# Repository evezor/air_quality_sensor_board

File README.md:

# Air Quality Sensor Board
board counts airborne particulate matter

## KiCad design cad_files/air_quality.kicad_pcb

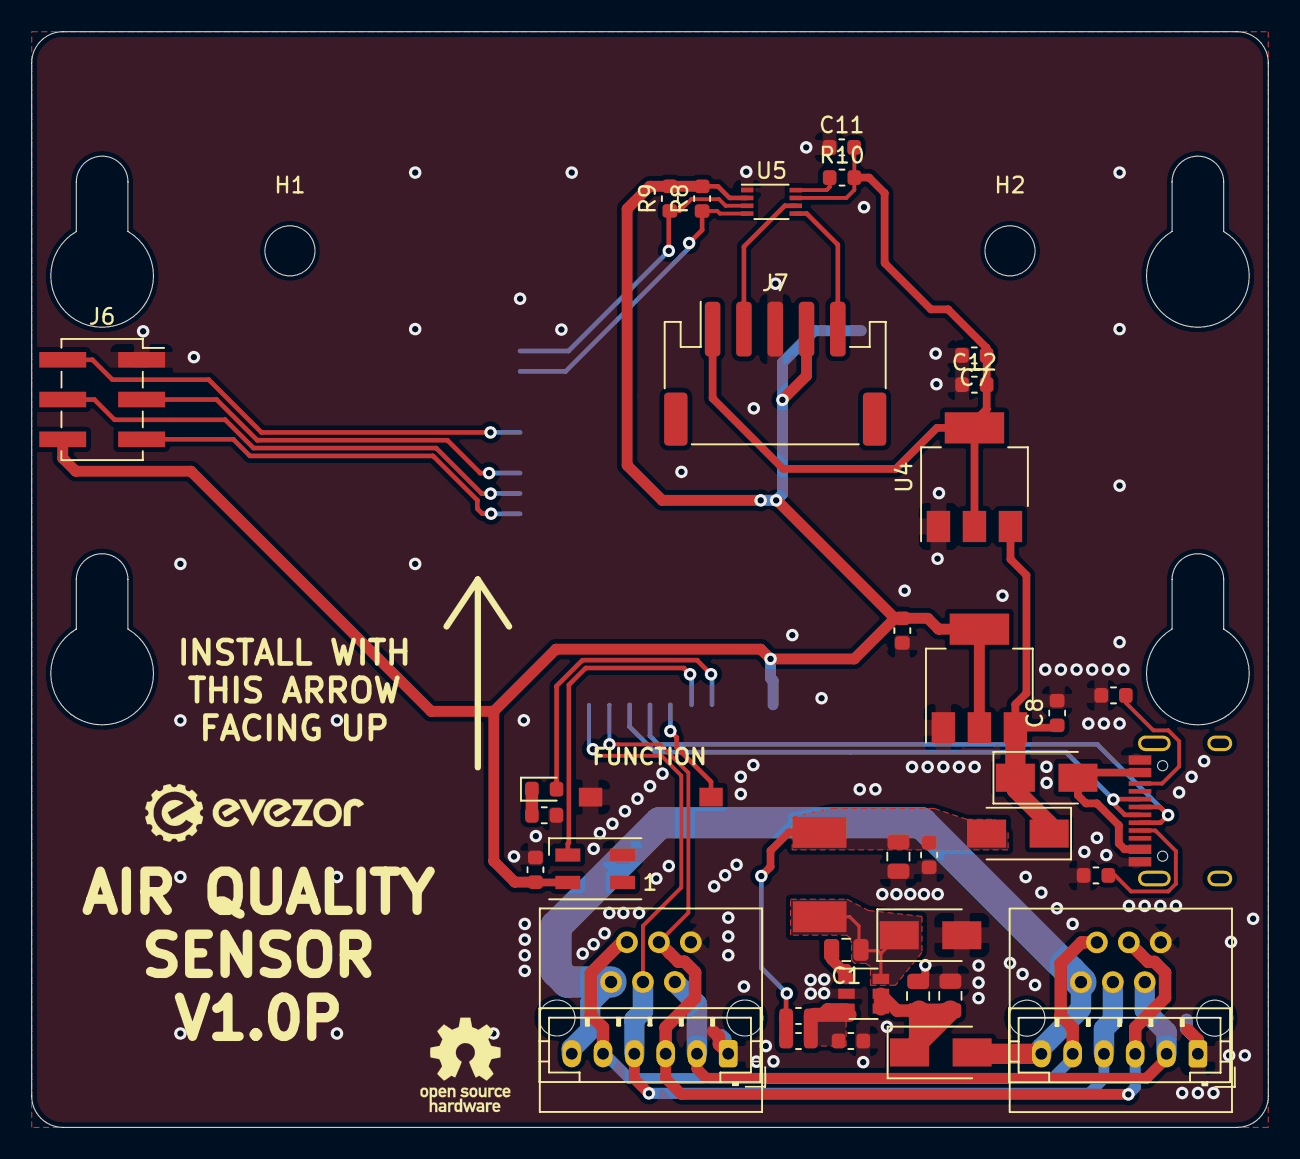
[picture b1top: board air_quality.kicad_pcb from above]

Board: 2 copper layers, 79.0 x 70.0 mm, 42 parts (1 on the bottom side), 32 nets.

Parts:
C1, C3: .1uF 100V; C_0805_2012Metric
C2, C5, C9, C10, C11, C12: .1uF; C_0603_1608Metric
C4: 4.7uF; C_0805_2012Metric
C6: 22uF; C_0805_2012Metric
C7, C8: 10uF; C_0603_1608Metric
D1, D2, D4, D5: SX35_SCHOTTKY; D_SMA
D3: LED; LED_0603_1608Metric
D6: SK6812MINI; LED_SK6812MINI_PLCC4_3.5x3.5mm_P1.75mm
H1: B5W-LD0101; AIR_QUALITY_B5W-LD0101
H2: MountingHole; MountingHole_3.2mm_M3
J1: USB_C_Receptacle_USB2.0; USB_C_Receptacle_HRO_TYPE-C-31-M-12
J2, J3: RJ11; RJ11_C189747_Horizontal
J4, J5: PH; JST_PH_B6B-PH-K_1x06_P2.00mm_Vertical
J6: Conn_02x03_Odd_Even; PinSocket_2x03_P2.54mm_Vertical_SMD
J7: Conn_01x05; JST_PH_S5B-PH-SM4-TB_1x05-1MP_P2.00mm_Horizontal
L1: 22uH; INDUCTOR_7.5X6.6_GCDA0630-220MC
R1: 10k; R_0603_1608Metric
R2: 82k; R_0603_1608Metric
R3, R4: 5.1k; R_0603_1608Metric
R5: 15k; R_0603_1608Metric
R8, R9: 2.2k; R_0603_1608Metric
R10: 200K; R_0603_1608Metric
SW1: SW_Push; SWITCH_2x3_SMD_TACTILE_GREEN
U1: SY8401ABC; SOT-23-6
U2: AMS1117-3.3; SOT-223-3_TabPin2
U3: EDGE_STM32F405_CPU_V1; EDGE_STAMP
U4: AMS1117-5.0; SOT-223-3_TabPin2
U5: LEVEL_SHIFTER_PCA9306; VSSOP-8_2.3x2mm_P0.5mm

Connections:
+3V3: C9.2, C10.1, D6.4, J6.6, J7.4, R8.2, R9.2, U2.2, U3.1, U3.18, U5.2
+5V: C7.1, C11.2, C12.2, J7.1, R10.2, U4.2, U5.7
/BOOT: J6.3, U3.36
/CAN_H: J2.3, J3.3, J4.3, J5.3, U3.26
/CAN_L: J2.4, J3.4, J4.4, J5.4, U3.27
/CC1: J1.A5, R4.1
/CC2: J1.B5, R3.1
/D+: J1.A6, J1.B6, U3.25
/D-: J1.A7, J1.B7, U3.24
/FD_H: J2.2, J3.2, J4.2, J5.2
/FD_L: J2.5, J3.5, J4.5, J5.5
/FUNCTION_BUTTON: SW1.1, U3.23
/HBT_LED: D3.2, U3.21
/NEO_STATUS: D6.3, U3.22
/OLED_SCL: J6.5, U3.34
/OLED_SDA: J6.4, U3.35
/OUT_1: R9.1, U3.42, U5.3
/OUT_2: R8.1, U3.41, U5.4
/RESET: J6.2, U3.38
/USB_VCC: D4.2, J1.A4, J1.A9, J1.B4, J1.B9
/VREG_OUT: C8.1, D4.1, D5.1, U2.3, U4.3
GND: C3.2, C4.2, C5.2, C6.2, C7.2, C8.2, C9.1, C10.2, C11.1, C12.1, D1.2, D6.2, J1.A1, J1.A12, J1.B1, J1.B12, J2.1, J3.1, J4.1, J5.1, J6.1, J7.3, R1.1, R3.2, R4.2, R5.1, SW1.2, U1.2, U2.1, U3.2, U3.17, U3.43, U4.1, U5.1
unnamed: C1.1, D1.1, L1.1, U1.6
unnamed: C1.2, U1.1
unnamed: C2.1, C5.1, C6.1, D5.2, L1.2, R2.1
unnamed: C2.2, R1.2, R2.2, U1.3
unnamed: C3.1, C4.1, D2.1, U1.4, U1.5
unnamed: D3.1, R5.2
unnamed: J7.2, U5.6
unnamed: J7.5, U5.5
unnamed: R10.1, U5.8
VBUS: D2.2, J2.6, J3.6, J4.6, J5.6

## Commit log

2020-12-11 Add cad files
